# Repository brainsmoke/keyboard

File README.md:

# A numpad-less keyboard with back lighting

TODO: find keycaps which look good with AND without backlight

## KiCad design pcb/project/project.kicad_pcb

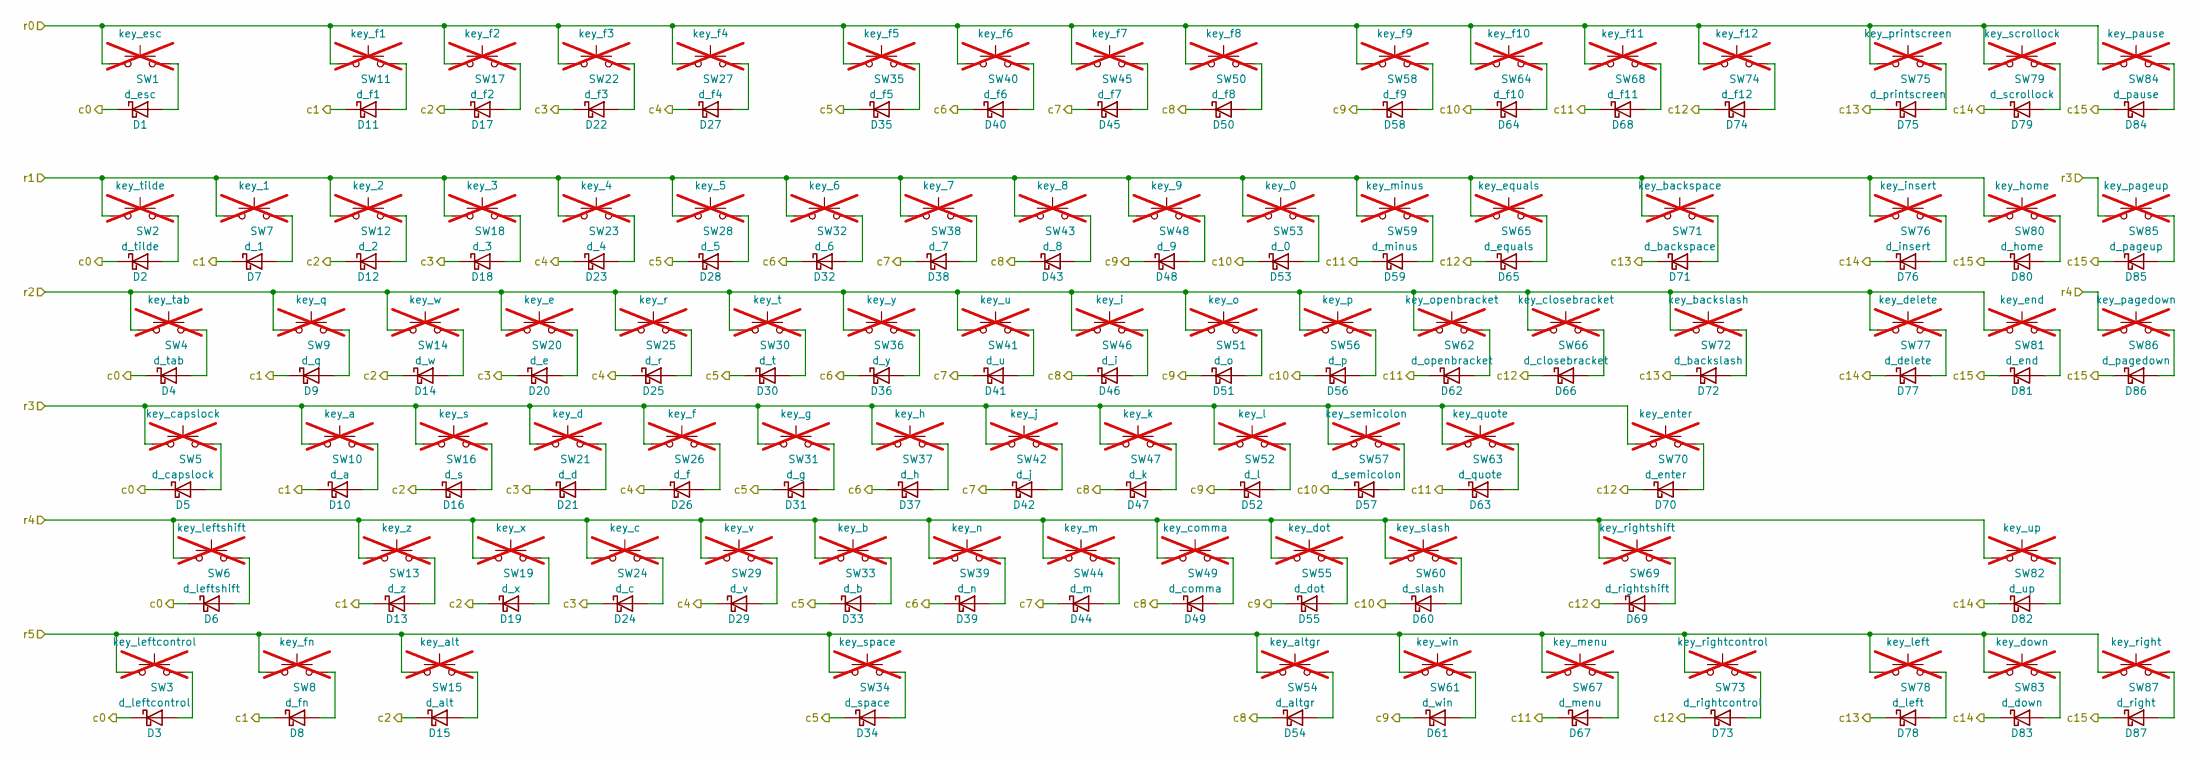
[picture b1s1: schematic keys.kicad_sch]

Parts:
D1: d_esc; D_SOD-123; LCSC C81598
D2: d_tilde; D_SOD-123; LCSC C81598
D3: d_leftcontrol; D_SOD-123; LCSC C81598
D4: d_tab; D_SOD-123; LCSC C81598
D5: d_capslock; D_SOD-123; LCSC C81598
D6: d_leftshift; D_SOD-123; LCSC C81598
D7: d_1; D_SOD-123; LCSC C81598
D8: d_fn; D_SOD-123; LCSC C81598
D9: d_q; D_SOD-123; LCSC C81598
D10: d_a; D_SOD-123; LCSC C81598
D11: d_f1; D_SOD-123; LCSC C81598
D12: d_2; D_SOD-123; LCSC C81598
D13: d_z; D_SOD-123; LCSC C81598
D14: d_w; D_SOD-123; LCSC C81598
D15: d_alt; D_SOD-123; LCSC C81598
D16: d_s; D_SOD-123; LCSC C81598
D17: d_f2; D_SOD-123; LCSC C81598
D18: d_3; D_SOD-123; LCSC C81598
D19: d_x; D_SOD-123; LCSC C81598
D20: d_e; D_SOD-123; LCSC C81598
D21: d_d; D_SOD-123; LCSC C81598
D22: d_f3; D_SOD-123; LCSC C81598
D23: d_4; D_SOD-123; LCSC C81598
D24: d_c; D_SOD-123; LCSC C81598
D25: d_r; D_SOD-123; LCSC C81598
D26: d_f; D_SOD-123; LCSC C81598
D27: d_f4; D_SOD-123; LCSC C81598
D28: d_5; D_SOD-123; LCSC C81598
D29: d_v; D_SOD-123; LCSC C81598
D30: d_t; D_SOD-123; LCSC C81598
D31: d_g; D_SOD-123; LCSC C81598
D32: d_6; D_SOD-123; LCSC C81598
D33: d_b; D_SOD-123; LCSC C81598
D34: d_space; D_SOD-123; LCSC C81598
D35: d_f5; D_SOD-123; LCSC C81598
D36: d_y; D_SOD-123; LCSC C81598
D37: d_h; D_SOD-123; LCSC C81598
D38: d_7; D_SOD-123; LCSC C81598
D39: d_n; D_SOD-123; LCSC C81598
D40: d_f6; D_SOD-123; LCSC C81598
D41: d_u; D_SOD-123; LCSC C81598
D42: d_j; D_SOD-123; LCSC C81598
D43: d_8; D_SOD-123; LCSC C81598
D44: d_m; D_SOD-123; LCSC C81598
D45: d_f7; D_SOD-123; LCSC C81598
D46: d_i; D_SOD-123; LCSC C81598
D47: d_k; D_SOD-123; LCSC C81598
D48: d_9; D_SOD-123; LCSC C81598
D49: d_comma; D_SOD-123; LCSC C81598
D50: d_f8; D_SOD-123; LCSC C81598
D51: d_o; D_SOD-123; LCSC C81598
D52: d_l; D_SOD-123; LCSC C81598
D53: d_0; D_SOD-123; LCSC C81598
D54: d_altgr; D_SOD-123; LCSC C81598
D55: d_dot; D_SOD-123; LCSC C81598
D56: d_p; D_SOD-123; LCSC C81598
D57: d_semicolon; D_SOD-123; LCSC C81598
D58: d_f9; D_SOD-123; LCSC C81598
D59: d_minus; D_SOD-123; LCSC C81598
D60: d_slash; D_SOD-123; LCSC C81598
D61: d_win; D_SOD-123; LCSC C81598
D62: d_openbracket; D_SOD-123; LCSC C81598
D63: d_quote; D_SOD-123; LCSC C81598
D64: d_f10; D_SOD-123; LCSC C81598
D65: d_equals; D_SOD-123; LCSC C81598
D66: d_closebracket; D_SOD-123; LCSC C81598
D67: d_menu; D_SOD-123; LCSC C81598
D68: d_f11; D_SOD-123; LCSC C81598
D69: d_rightshift; D_SOD-123; LCSC C81598
D70: d_enter; D_SOD-123; LCSC C81598
D71: d_backspace; D_SOD-123; LCSC C81598
D72: d_backslash; D_SOD-123; LCSC C81598
D73: d_rightcontrol; D_SOD-123; LCSC C81598
D74: d_f12; D_SOD-123; LCSC C81598
D75: d_printscreen; D_SOD-123; LCSC C81598
D76: d_insert; D_SOD-123; LCSC C81598
D77: d_delete; D_SOD-123; LCSC C81598
D78: d_left; D_SOD-123; LCSC C81598
D79: d_scrollock; D_SOD-123; LCSC C81598
D80: d_home; D_SOD-123; LCSC C81598
D81: d_end; D_SOD-123; LCSC C81598
D82: d_up; D_SOD-123; LCSC C81598
D83: d_down; D_SOD-123; LCSC C81598
D84: d_pause; D_SOD-123; LCSC C81598
D85: d_pageup; D_SOD-123; LCSC C81598
D86: d_pagedown; D_SOD-123; LCSC C81598
D87: d_right; D_SOD-123; LCSC C81598
SW1: key_esc; SW_Cherry_MX_1.00u_PCB; not fitted
SW2: key_tilde; SW_Cherry_MX_1.00u_PCB; not fitted
SW3: key_leftcontrol; SW_Cherry_MX_1.25u_PCB; not fitted
SW4: key_tab; SW_Cherry_MX_1.50u_PCB; not fitted
SW5: key_capslock; SW_Cherry_MX_1.75u_PCB; not fitted
SW6: key_leftshift; SW_Cherry_MX_2.25u_PCB; not fitted
SW7: key_1; SW_Cherry_MX_1.00u_PCB; not fitted
SW8: key_fn; SW_Cherry_MX_1.25u_PCB; not fitted
SW9: key_q; SW_Cherry_MX_1.00u_PCB; not fitted
SW10: key_a; SW_Cherry_MX_1.00u_PCB; not fitted
SW11: key_f1; SW_Cherry_MX_1.00u_PCB; not fitted
SW12: key_2; SW_Cherry_MX_1.00u_PCB; not fitted
SW13: key_z; SW_Cherry_MX_1.00u_PCB; not fitted
SW14: key_w; SW_Cherry_MX_1.00u_PCB; not fitted
SW15: key_alt; SW_Cherry_MX_1.25u_PCB; not fitted
SW16: key_s; SW_Cherry_MX_1.00u_PCB; not fitted
SW17: key_f2; SW_Cherry_MX_1.00u_PCB; not fitted
SW18: key_3; SW_Cherry_MX_1.00u_PCB; not fitted
SW19: key_x; SW_Cherry_MX_1.00u_PCB; not fitted
SW20: key_e; SW_Cherry_MX_1.00u_PCB; not fitted
SW21: key_d; SW_Cherry_MX_1.00u_PCB; not fitted
SW22: key_f3; SW_Cherry_MX_1.00u_PCB; not fitted
SW23: key_4; SW_Cherry_MX_1.00u_PCB; not fitted
SW24: key_c; SW_Cherry_MX_1.00u_PCB; not fitted
SW25: key_r; SW_Cherry_MX_1.00u_PCB; not fitted
SW26: key_f; SW_Cherry_MX_1.00u_PCB; not fitted
SW27: key_f4; SW_Cherry_MX_1.00u_PCB; not fitted
SW28: key_5; SW_Cherry_MX_1.00u_PCB; not fitted
SW29: key_v; SW_Cherry_MX_1.00u_PCB; not fitted
SW30: key_t; SW_Cherry_MX_1.00u_PCB; not fitted
SW31: key_g; SW_Cherry_MX_1.00u_PCB; not fitted
SW32: key_6; SW_Cherry_MX_1.00u_PCB; not fitted
SW33: key_b; SW_Cherry_MX_1.00u_PCB; not fitted
SW34: key_space; SW_Cherry_MX_6.25u_PCB; not fitted
SW35: key_f5; SW_Cherry_MX_1.00u_PCB; not fitted
SW36: key_y; SW_Cherry_MX_1.00u_PCB; not fitted
SW37: key_h; SW_Cherry_MX_1.00u_PCB; not fitted
SW38: key_7; SW_Cherry_MX_1.00u_PCB; not fitted
SW39: key_n; SW_Cherry_MX_1.00u_PCB; not fitted
SW40: key_f6; SW_Cherry_MX_1.00u_PCB; not fitted
SW41: key_u; SW_Cherry_MX_1.00u_PCB; not fitted
SW42: key_j; SW_Cherry_MX_1.00u_PCB; not fitted
SW43: key_8; SW_Cherry_MX_1.00u_PCB; not fitted
SW44: key_m; SW_Cherry_MX_1.00u_PCB; not fitted
SW45: key_f7; SW_Cherry_MX_1.00u_PCB; not fitted
SW46: key_i; SW_Cherry_MX_1.00u_PCB; not fitted
SW47: key_k; SW_Cherry_MX_1.00u_PCB; not fitted
SW48: key_9; SW_Cherry_MX_1.00u_PCB; not fitted
SW49: key_comma; SW_Cherry_MX_1.00u_PCB; not fitted
SW50: key_f8; SW_Cherry_MX_1.00u_PCB; not fitted
SW51: key_o; SW_Cherry_MX_1.00u_PCB; not fitted
SW52: key_l; SW_Cherry_MX_1.00u_PCB; not fitted
SW53: key_0; SW_Cherry_MX_1.00u_PCB; not fitted
SW54: key_altgr; SW_Cherry_MX_1.25u_PCB; not fitted
SW55: key_dot; SW_Cherry_MX_1.00u_PCB; not fitted
SW56: key_p; SW_Cherry_MX_1.00u_PCB; not fitted
SW57: key_semicolon; SW_Cherry_MX_1.00u_PCB; not fitted
SW58: key_f9; SW_Cherry_MX_1.00u_PCB; not fitted
SW59: key_minus; SW_Cherry_MX_1.00u_PCB; not fitted
SW60: key_slash; SW_Cherry_MX_1.00u_PCB; not fitted
SW61: key_win; SW_Cherry_MX_1.25u_PCB; not fitted
SW62: key_openbracket; SW_Cherry_MX_1.00u_PCB; not fitted
SW63: key_quote; SW_Cherry_MX_1.00u_PCB; not fitted
SW64: key_f10; SW_Cherry_MX_1.00u_PCB; not fitted
SW65: key_equals; SW_Cherry_MX_1.00u_PCB; not fitted
SW66: key_closebracket; SW_Cherry_MX_1.00u_PCB; not fitted
SW67: key_menu; SW_Cherry_MX_1.25u_PCB; not fitted
SW68: key_f11; SW_Cherry_MX_1.00u_PCB; not fitted
SW69: key_rightshift; SW_Cherry_MX_2.75u_PCB; not fitted
SW70: key_enter; SW_Cherry_MX_2.25u_PCB; not fitted
SW71: key_backspace; SW_Cherry_MX_2.00u_PCB; not fitted
SW72: key_backslash; SW_Cherry_MX_1.50u_PCB; not fitted
SW73: key_rightcontrol; SW_Cherry_MX_1.25u_PCB; not fitted
SW74: key_f12; SW_Cherry_MX_1.00u_PCB; not fitted
SW75: key_printscreen; SW_Cherry_MX_1.00u_PCB; not fitted
SW76: key_insert; SW_Cherry_MX_1.00u_PCB; not fitted
SW77: key_delete; SW_Cherry_MX_1.00u_PCB; not fitted
SW78: key_left; SW_Cherry_MX_1.00u_PCB; not fitted
SW79: key_scrollock; SW_Cherry_MX_1.00u_PCB; not fitted
SW80: key_home; SW_Cherry_MX_1.00u_PCB; not fitted
SW81: key_end; SW_Cherry_MX_1.00u_PCB; not fitted
SW82: key_up; SW_Cherry_MX_1.00u_PCB; not fitted
SW83: key_down; SW_Cherry_MX_1.00u_PCB; not fitted
SW84: key_pause; SW_Cherry_MX_1.00u_PCB; not fitted
SW85: key_pageup; SW_Cherry_MX_1.00u_PCB; not fitted
SW86: key_pagedown; SW_Cherry_MX_1.00u_PCB; not fitted
SW87: key_right; SW_Cherry_MX_1.00u_PCB; not fitted

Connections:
/C0: D1.1 (K), D2.1 (K), D3.1 (K), D4.1 (K), D5.1 (K), D6.1 (K); also elsewhere on the board
/C1: D7.1 (K), D8.1 (K), D9.1 (K), D10.1 (K), D11.1 (K), D13.1 (K); also elsewhere on the board
/C2: D12.1 (K), D14.1 (K), D15.1 (K), D16.1 (K), D17.1 (K), D19.1 (K); also elsewhere on the board
/C3: D18.1 (K), D20.1 (K), D21.1 (K), D22.1 (K), D24.1 (K); also elsewhere on the board
/C4: D23.1 (K), D25.1 (K), D26.1 (K), D27.1 (K), D29.1 (K); also elsewhere on the board
/C5: D28.1 (K), D30.1 (K), D31.1 (K), D33.1 (K), D34.1 (K), D35.1 (K); also elsewhere on the board
/C6: D32.1 (K), D36.1 (K), D37.1 (K), D39.1 (K), D40.1 (K); also elsewhere on the board
/C7: D38.1 (K), D41.1 (K), D42.1 (K), D44.1 (K), D45.1 (K); also elsewhere on the board
/C8: D43.1 (K), D46.1 (K), D47.1 (K), D49.1 (K), D50.1 (K), D54.1 (K); also elsewhere on the board
/C9: D48.1 (K), D51.1 (K), D52.1 (K), D55.1 (K), D58.1 (K), D61.1 (K); also elsewhere on the board
/C10: D53.1 (K), D56.1 (K), D57.1 (K), D60.1 (K), D64.1 (K); also elsewhere on the board
/C11: D59.1 (K), D62.1 (K), D63.1 (K), D67.1 (K), D68.1 (K); also elsewhere on the board
/C12: D65.1 (K), D66.1 (K), D69.1 (K), D70.1 (K), D73.1 (K), D74.1 (K); also elsewhere on the board
/C13: D71.1 (K), D72.1 (K), D75.1 (K), D78.1 (K); also elsewhere on the board
/C14: D76.1 (K), D77.1 (K), D79.1 (K), D82.1 (K), D83.1 (K); also elsewhere on the board
/C15: D80.1 (K), D81.1 (K), D84.1 (K), D85.1 (K), D86.1 (K), D87.1 (K); also elsewhere on the board
/R0: SW1.1, SW11.1, SW17.1, SW22.1, SW27.1, SW35.1, SW40.1, SW45.1, SW50.1, SW58.1, SW64.1, SW68.1, SW74.1, SW75.1, SW79.1, SW84.1; also elsewhere on the board
/R1: SW2.1, SW7.1, SW12.1, SW18.1, SW23.1, SW28.1, SW32.1, SW38.1, SW43.1, SW48.1, SW53.1, SW59.1, SW65.1, SW71.1, SW76.1, SW80.1; also elsewhere on the board
/R2: SW4.1, SW9.1, SW14.1, SW20.1, SW25.1, SW30.1, SW36.1, SW41.1, SW46.1, SW51.1, SW56.1, SW62.1, SW66.1, SW72.1, SW77.1, SW81.1; also elsewhere on the board
/R3: SW5.1, SW10.1, SW16.1, SW21.1, SW26.1, SW31.1, SW37.1, SW42.1, SW47.1, SW52.1, SW57.1, SW63.1, SW70.1, SW85.1; also elsewhere on the board
/R4: SW6.1, SW13.1, SW19.1, SW24.1, SW29.1, SW33.1, SW39.1, SW44.1, SW49.1, SW55.1, SW60.1, SW69.1, SW82.1, SW86.1; also elsewhere on the board
/R5: SW3.1, SW8.1, SW15.1, SW34.1, SW54.1, SW61.1, SW67.1, SW73.1, SW78.1, SW83.1, SW87.1; also elsewhere on the board
unnamed: D1.2 (A), SW1.2
unnamed: D2.2 (A), SW2.2
unnamed: D3.2 (A), SW3.2
unnamed: D4.2 (A), SW4.2
unnamed: D5.2 (A), SW5.2
unnamed: D6.2 (A), SW6.2
unnamed: D7.2 (A), SW7.2
unnamed: D8.2 (A), SW8.2
unnamed: D9.2 (A), SW9.2
unnamed: D10.2 (A), SW10.2
unnamed: D11.2 (A), SW11.2
unnamed: D12.2 (A), SW12.2
unnamed: D13.2 (A), SW13.2
unnamed: D14.2 (A), SW14.2
unnamed: D15.2 (A), SW15.2
unnamed: D16.2 (A), SW16.2
unnamed: D17.2 (A), SW17.2
unnamed: D18.2 (A), SW18.2
unnamed: D19.2 (A), SW19.2
unnamed: D20.2 (A), SW20.2
unnamed: D21.2 (A), SW21.2
unnamed: D22.2 (A), SW22.2
unnamed: D23.2 (A), SW23.2
unnamed: D24.2 (A), SW24.2
unnamed: D25.2 (A), SW25.2
unnamed: D26.2 (A), SW26.2
unnamed: D27.2 (A), SW27.2
unnamed: D28.2 (A), SW28.2
unnamed: D29.2 (A), SW29.2
unnamed: D30.2 (A), SW30.2
unnamed: D31.2 (A), SW31.2
unnamed: D32.2 (A), SW32.2
unnamed: D33.2 (A), SW33.2
unnamed: D34.2 (A), SW34.2
unnamed: D35.2 (A), SW35.2
unnamed: D36.2 (A), SW36.2
unnamed: D37.2 (A), SW37.2
unnamed: D38.2 (A), SW38.2
unnamed: D39.2 (A), SW39.2
unnamed: D40.2 (A), SW40.2
unnamed: D41.2 (A), SW41.2
unnamed: D42.2 (A), SW42.2
unnamed: D43.2 (A), SW43.2
unnamed: D44.2 (A), SW44.2
unnamed: D45.2 (A), SW45.2
unnamed: D46.2 (A), SW46.2
unnamed: D47.2 (A), SW47.2
unnamed: D48.2 (A), SW48.2
unnamed: D49.2 (A), SW49.2
unnamed: D50.2 (A), SW50.2
unnamed: D51.2 (A), SW51.2
unnamed: D52.2 (A), SW52.2
unnamed: D53.2 (A), SW53.2
unnamed: D54.2 (A), SW54.2
unnamed: D55.2 (A), SW55.2
unnamed: D56.2 (A), SW56.2
unnamed: D57.2 (A), SW57.2
unnamed: D58.2 (A), SW58.2
unnamed: D59.2 (A), SW59.2
unnamed: D60.2 (A), SW60.2
unnamed: D61.2 (A), SW61.2
unnamed: D62.2 (A), SW62.2
unnamed: D63.2 (A), SW63.2
unnamed: D64.2 (A), SW64.2
unnamed: D65.2 (A), SW65.2
unnamed: D66.2 (A), SW66.2
unnamed: D67.2 (A), SW67.2
unnamed: D68.2 (A), SW68.2
unnamed: D69.2 (A), SW69.2
unnamed: D70.2 (A), SW70.2
unnamed: D71.2 (A), SW71.2
unnamed: D72.2 (A), SW72.2
unnamed: D73.2 (A), SW73.2
unnamed: D74.2 (A), SW74.2
unnamed: D75.2 (A), SW75.2
unnamed: D76.2 (A), SW76.2
unnamed: D77.2 (A), SW77.2
unnamed: D78.2 (A), SW78.2
unnamed: D79.2 (A), SW79.2
unnamed: D80.2 (A), SW80.2
unnamed: D81.2 (A), SW81.2
unnamed: D82.2 (A), SW82.2
unnamed: D83.2 (A), SW83.2
unnamed: D84.2 (A), SW84.2
unnamed: D85.2 (A), SW85.2
unnamed: D86.2 (A), SW86.2
unnamed: D87.2 (A), SW87.2

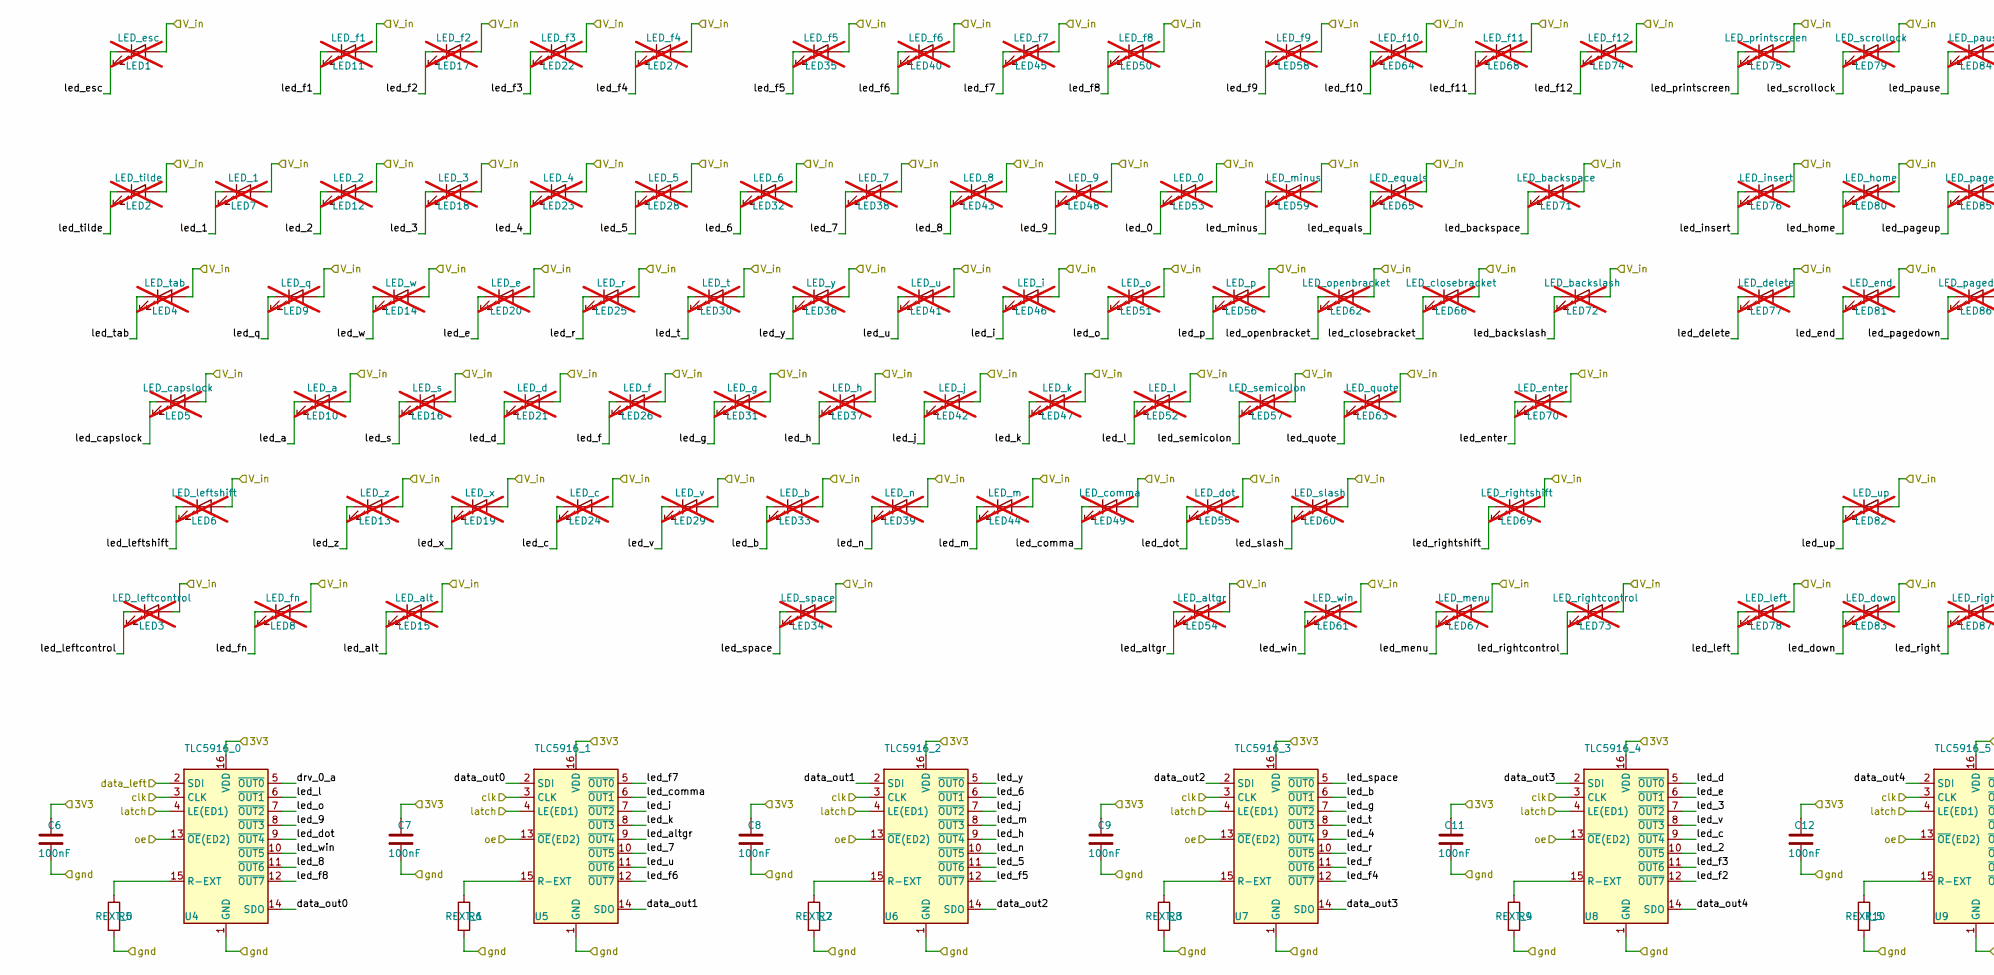
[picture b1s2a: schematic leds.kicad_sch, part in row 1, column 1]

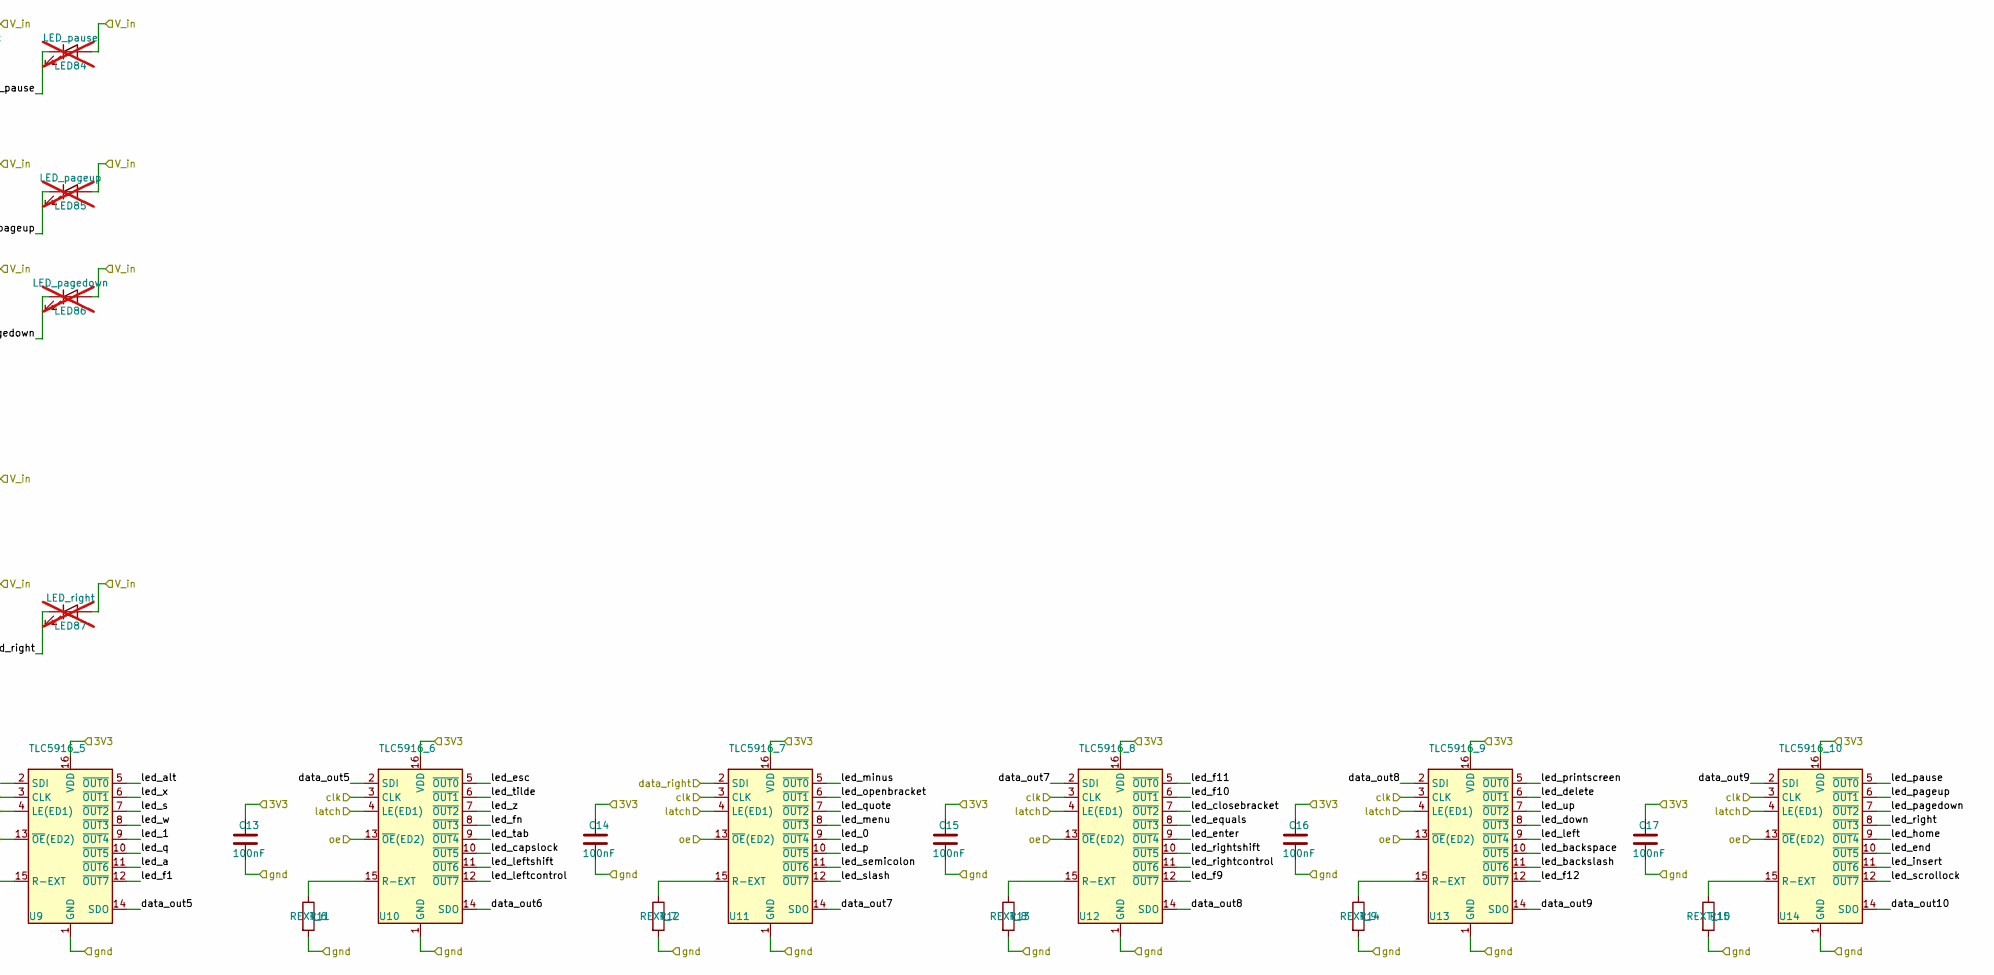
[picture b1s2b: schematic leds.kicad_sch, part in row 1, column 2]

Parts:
C6, C7, C8, C9, C11, C12, C13, C14, C15, C16, C17: 100nF; C_0402_1005Metric; LCSC C1525
LED1: LED_esc; LED3mm; not fitted
LED2: LED_tilde; LED3mm; not fitted
LED3: LED_leftcontrol; LED3mm; not fitted
LED4: LED_tab; LED3mm; not fitted
LED5: LED_capslock; LED3mm; not fitted
LED6: LED_leftshift; LED3mm; not fitted
LED7: LED_1; LED3mm; not fitted
LED8: LED_fn; LED3mm; not fitted
LED9: LED_q; LED3mm; not fitted
LED10: LED_a; LED3mm; not fitted
LED11: LED_f1; LED3mm; not fitted
LED12: LED_2; LED3mm; not fitted
LED13: LED_z; LED3mm; not fitted
LED14: LED_w; LED3mm; not fitted
LED15: LED_alt; LED3mm; not fitted
LED16: LED_s; LED3mm; not fitted
LED17: LED_f2; LED3mm; not fitted
LED18: LED_3; LED3mm; not fitted
LED19: LED_x; LED3mm; not fitted
LED20: LED_e; LED3mm; not fitted
LED21: LED_d; LED3mm; not fitted
LED22: LED_f3; LED3mm; not fitted
LED23: LED_4; LED3mm; not fitted
LED24: LED_c; LED3mm; not fitted
LED25: LED_r; LED3mm; not fitted
LED26: LED_f; LED3mm; not fitted
LED27: LED_f4; LED3mm; not fitted
LED28: LED_5; LED3mm; not fitted
LED29: LED_v; LED3mm; not fitted
LED30: LED_t; LED3mm; not fitted
LED31: LED_g; LED3mm; not fitted
LED32: LED_6; LED3mm; not fitted
LED33: LED_b; LED3mm; not fitted
LED34: LED_space; LED3mm; not fitted
LED35: LED_f5; LED3mm; not fitted
LED36: LED_y; LED3mm; not fitted
LED37: LED_h; LED3mm; not fitted
LED38: LED_7; LED3mm; not fitted
LED39: LED_n; LED3mm; not fitted
LED40: LED_f6; LED3mm; not fitted
LED41: LED_u; LED3mm; not fitted
LED42: LED_j; LED3mm; not fitted
LED43: LED_8; LED3mm; not fitted
LED44: LED_m; LED3mm; not fitted
LED45: LED_f7; LED3mm; not fitted
LED46: LED_i; LED3mm; not fitted
LED47: LED_k; LED3mm; not fitted
LED48: LED_9; LED3mm; not fitted
LED49: LED_comma; LED3mm; not fitted
LED50: LED_f8; LED3mm; not fitted
LED51: LED_o; LED3mm; not fitted
LED52: LED_l; LED3mm; not fitted
LED53: LED_0; LED3mm; not fitted
LED54: LED_altgr; LED3mm; not fitted
LED55: LED_dot; LED3mm; not fitted
LED56: LED_p; LED3mm; not fitted
LED57: LED_semicolon; LED3mm; not fitted
LED58: LED_f9; LED3mm; not fitted
LED59: LED_minus; LED3mm; not fitted
LED60: LED_slash; LED3mm; not fitted
LED61: LED_win; LED3mm; not fitted
LED62: LED_openbracket; LED3mm; not fitted
LED63: LED_quote; LED3mm; not fitted
LED64: LED_f10; LED3mm; not fitted
LED65: LED_equals; LED3mm; not fitted
LED66: LED_closebracket; LED3mm; not fitted
LED67: LED_menu; LED3mm; not fitted
LED68: LED_f11; LED3mm; not fitted
LED69: LED_rightshift; LED3mm; not fitted
LED70: LED_enter; LED3mm; not fitted
LED71: LED_backspace; LED3mm; not fitted
LED72: LED_backslash; LED3mm; not fitted
LED73: LED_rightcontrol; LED3mm; not fitted
LED74: LED_f12; LED3mm; not fitted
LED75: LED_printscreen; LED3mm; not fitted
LED76: LED_insert; LED3mm; not fitted
LED77: LED_delete; LED3mm; not fitted
LED78: LED_left; LED3mm; not fitted
LED79: LED_scrollock; LED3mm; not fitted
LED80: LED_home; LED3mm; not fitted
LED81: LED_end; LED3mm; not fitted
LED82: LED_up; LED3mm; not fitted
LED83: LED_down; LED3mm; not fitted
LED84: LED_pause; LED3mm; not fitted
LED85: LED_pageup; LED3mm; not fitted
LED86: LED_pagedown; LED3mm; not fitted
LED87: LED_right; LED3mm; not fitted
R5: REXT_0; R_0402_1005Metric; LCSC C25905
R6: REXT_1; R_0402_1005Metric; LCSC C25905
R7: REXT_2; R_0402_1005Metric; LCSC C25905
R8: REXT_3; R_0402_1005Metric; LCSC C25905
R9: REXT_4; R_0402_1005Metric; LCSC C25905
R10: REXT_5; R_0402_1005Metric; LCSC C25905
R11: REXT_6; R_0402_1005Metric; LCSC C25905
R12: REXT_7; R_0402_1005Metric; LCSC C25905
R13: REXT_8; R_0402_1005Metric; LCSC C25905
R14: REXT_9; R_0402_1005Metric; LCSC C25905
R15: REXT_10; R_0402_1005Metric; LCSC C25905
U4: TLC5916_0; TSSOP-16_4.4x5mm_P0.65mm; LCSC C2678539
U5: TLC5916_1; TSSOP-16_4.4x5mm_P0.65mm; LCSC C2678539
U6: TLC5916_2; TSSOP-16_4.4x5mm_P0.65mm; LCSC C2678539
U7: TLC5916_3; TSSOP-16_4.4x5mm_P0.65mm; LCSC C2678539
U8: TLC5916_4; TSSOP-16_4.4x5mm_P0.65mm; LCSC C2678539
U9: TLC5916_5; TSSOP-16_4.4x5mm_P0.65mm; LCSC C2678539
U10: TLC5916_6; TSSOP-16_4.4x5mm_P0.65mm; LCSC C2678539
U11: TLC5916_7; TSSOP-16_4.4x5mm_P0.65mm; LCSC C2678539
U12: TLC5916_8; TSSOP-16_4.4x5mm_P0.65mm; LCSC C2678539
U13: TLC5916_9; TSSOP-16_4.4x5mm_P0.65mm; LCSC C2678539
U14: TLC5916_10; TSSOP-16_4.4x5mm_P0.65mm; LCSC C2678539

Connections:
3V3: C6.1, C7.1, C8.1, C9.1, C11.1, C12.1, C13.1, C14.1, C15.1, C16.1, C17.1, U4.16 (VDD), U5.16 (VDD), U6.16 (VDD), U7.16 (VDD), U8.16 (VDD), U9.16 (VDD), U10.16 (VDD), U11.16 (VDD), U12.16 (VDD), U13.16 (VDD), U14.16 (VDD); also elsewhere on the board
5V: LED1.2 (A), LED2.2 (A), LED3.2 (A), LED4.2 (A), LED5.2 (A), LED6.2 (A), LED7.2 (A), LED8.2 (A), LED9.2 (A), LED10.2 (A), LED11.2 (A), LED12.2 (A), LED13.2 (A), LED14.2 (A), LED15.2 (A), LED16.2 (A), LED17.2 (A), LED18.2 (A), LED19.2 (A), LED20.2 (A), LED21.2 (A), LED22.2 (A), LED23.2 (A), LED24.2 (A), LED25.2 (A), LED26.2 (A), LED27.2 (A), LED28.2 (A), LED29.2 (A), LED30.2 (A), LED31.2 (A), LED32.2 (A), LED33.2 (A), LED34.2 (A), LED35.2 (A), LED36.2 (A), LED37.2 (A), LED38.2 (A), LED39.2 (A), LED40.2 (A), LED41.2 (A), LED42.2 (A), LED43.2 (A), LED44.2 (A), LED45.2 (A), LED46.2 (A), LED47.2 (A), LED48.2 (A), LED49.2 (A), LED50.2 (A), LED51.2 (A), LED52.2 (A), LED53.2 (A), LED54.2 (A), LED55.2 (A), LED56.2 (A), LED57.2 (A), LED58.2 (A), LED59.2 (A), LED60.2 (A), LED61.2 (A), LED62.2 (A), LED63.2 (A), LED64.2 (A), LED65.2 (A), LED66.2 (A), LED67.2 (A), LED68.2 (A), LED69.2 (A), LED70.2 (A), LED71.2 (A), LED72.2 (A), LED73.2 (A), LED74.2 (A), LED75.2 (A), LED76.2 (A), LED77.2 (A), LED78.2 (A), LED79.2 (A), LED80.2 (A), LED81.2 (A), LED82.2 (A), LED83.2 (A), LED84.2 (A), LED85.2 (A), LED86.2 (A), LED87.2 (A); also elsewhere on the board
/LEDs/clk: U4.3 (CLK), U5.3 (CLK), U6.3 (CLK), U7.3 (CLK), U8.3 (CLK), U9.3 (CLK), U10.3 (CLK), U11.3 (CLK), U12.3 (CLK), U13.3 (CLK), U14.3 (CLK); also elsewhere on the board
/LEDs/data_left: U4.2 (SDI); also elsewhere on the board
/LEDs/data_out0: U4.14 (SDO), U5.2 (SDI)
/LEDs/data_out1: U5.14 (SDO), U6.2 (SDI)
/LEDs/data_out2: U6.14 (SDO), U7.2 (SDI)
/LEDs/data_out3: U7.14 (SDO), U8.2 (SDI)
/LEDs/data_out4: U8.14 (SDO), U9.2 (SDI)
/LEDs/data_out5: U9.14 (SDO), U10.2 (SDI)
/LEDs/data_out6: U10.14 (SDO)
/LEDs/data_out7: U11.14 (SDO), U12.2 (SDI)
/LEDs/data_out8: U12.14 (SDO), U13.2 (SDI)
/LEDs/data_out9: U13.14 (SDO), U14.2 (SDI)
/LEDs/data_out10: U14.14 (SDO)
/LEDs/data_right: U11.2 (SDI); also elsewhere on the board
/LEDs/drv_0_a: U4.5 (~OUT0)
/LEDs/latch: U4.4 (LE(ED1)), U5.4 (LE(ED1)), U6.4 (LE(ED1)), U7.4 (LE(ED1)), U8.4 (LE(ED1)), U9.4 (LE(ED1)), U10.4 (LE(ED1)), U11.4 (LE(ED1)), U12.4 (LE(ED1)), U13.4 (LE(ED1)), U14.4 (LE(ED1)); also elsewhere on the board
/LEDs/led_0: LED53.1 (K), U11.9 (~OUT4)
/LEDs/led_1: LED7.1 (K), U9.9 (~OUT4)
/LEDs/led_2: LED12.1 (K), U8.10 (~OUT5)
/LEDs/led_3: LED18.1 (K), U8.7 (~OUT2)
/LEDs/led_4: LED23.1 (K), U7.9 (~OUT4)
/LEDs/led_5: LED28.1 (K), U6.11 (~OUT6)
/LEDs/led_6: LED32.1 (K), U6.6 (~OUT1)
/LEDs/led_7: LED38.1 (K), U5.10 (~OUT5)
/LEDs/led_8: LED43.1 (K), U4.11 (~OUT6)
/LEDs/led_9: LED48.1 (K), U4.8 (~OUT3)
/LEDs/led_a: LED10.1 (K), U9.11 (~OUT6)
/LEDs/led_alt: LED15.1 (K), U9.5 (~OUT0)
/LEDs/led_altgr: LED54.1 (K), U5.9 (~OUT4)
/LEDs/led_b: LED33.1 (K), U7.6 (~OUT1)
/LEDs/led_backslash: LED72.1 (K), U13.11 (~OUT6)
/LEDs/led_backspace: LED71.1 (K), U13.10 (~OUT5)
/LEDs/led_c: LED24.1 (K), U8.9 (~OUT4)
/LEDs/led_capslock: LED5.1 (K), U10.10 (~OUT5)
/LEDs/led_closebracket: LED66.1 (K), U12.7 (~OUT2)
/LEDs/led_comma: LED49.1 (K), U5.6 (~OUT1)
/LEDs/led_d: LED21.1 (K), U8.5 (~OUT0)
/LEDs/led_delete: LED77.1 (K), U13.6 (~OUT1)
/LEDs/led_dot: LED55.1 (K), U4.9 (~OUT4)
/LEDs/led_down: LED83.1 (K), U13.8 (~OUT3)
/LEDs/led_e: LED20.1 (K), U8.6 (~OUT1)
/LEDs/led_end: LED81.1 (K), U14.10 (~OUT5)
/LEDs/led_enter: LED70.1 (K), U12.9 (~OUT4)
/LEDs/led_equals: LED65.1 (K), U12.8 (~OUT3)
/LEDs/led_esc: LED1.1 (K), U10.5 (~OUT0)
/LEDs/led_f: LED26.1 (K), U7.11 (~OUT6)
/LEDs/led_f1: LED11.1 (K), U9.12 (~OUT7)
/LEDs/led_f2: LED17.1 (K), U8.12 (~OUT7)
/LEDs/led_f3: LED22.1 (K), U8.11 (~OUT6)
/LEDs/led_f4: LED27.1 (K), U7.12 (~OUT7)
/LEDs/led_f5: LED35.1 (K), U6.12 (~OUT7)
/LEDs/led_f6: LED40.1 (K), U5.12 (~OUT7)
/LEDs/led_f7: LED45.1 (K), U5.5 (~OUT0)
/LEDs/led_f8: LED50.1 (K), U4.12 (~OUT7)
/LEDs/led_f9: LED58.1 (K), U12.12 (~OUT7)
/LEDs/led_f10: LED64.1 (K), U12.6 (~OUT1)
/LEDs/led_f11: LED68.1 (K), U12.5 (~OUT0)
/LEDs/led_f12: LED74.1 (K), U13.12 (~OUT7)
/LEDs/led_fn: LED8.1 (K), U10.8 (~OUT3)
/LEDs/led_g: LED31.1 (K), U7.7 (~OUT2)
/LEDs/led_h: LED37.1 (K), U6.9 (~OUT4)
/LEDs/led_home: LED80.1 (K), U14.9 (~OUT4)
/LEDs/led_i: LED46.1 (K), U5.7 (~OUT2)
/LEDs/led_insert: LED76.1 (K), U14.11 (~OUT6)
/LEDs/led_j: LED42.1 (K), U6.7 (~OUT2)
/LEDs/led_k: LED47.1 (K), U5.8 (~OUT3)
/LEDs/led_l: LED52.1 (K), U4.6 (~OUT1)
/LEDs/led_left: LED78.1 (K), U13.9 (~OUT4)
/LEDs/led_leftcontrol: LED3.1 (K), U10.12 (~OUT7)
/LEDs/led_leftshift: LED6.1 (K), U10.11 (~OUT6)
/LEDs/led_m: LED44.1 (K), U6.8 (~OUT3)
/LEDs/led_menu: LED67.1 (K), U11.8 (~OUT3)
/LEDs/led_minus: LED59.1 (K), U11.5 (~OUT0)
/LEDs/led_n: LED39.1 (K), U6.10 (~OUT5)
/LEDs/led_o: LED51.1 (K), U4.7 (~OUT2)
/LEDs/led_openbracket: LED62.1 (K), U11.6 (~OUT1)
/LEDs/led_p: LED56.1 (K), U11.10 (~OUT5)
/LEDs/led_pagedown: LED86.1 (K), U14.7 (~OUT2)
/LEDs/led_pageup: LED85.1 (K), U14.6 (~OUT1)
/LEDs/led_pause: LED84.1 (K), U14.5 (~OUT0)
/LEDs/led_printscreen: LED75.1 (K), U13.5 (~OUT0)
/LEDs/led_q: LED9.1 (K), U9.10 (~OUT5)
/LEDs/led_quote: LED63.1 (K), U11.7 (~OUT2)
/LEDs/led_r: LED25.1 (K), U7.10 (~OUT5)
/LEDs/led_right: LED87.1 (K), U14.8 (~OUT3)
/LEDs/led_rightcontrol: LED73.1 (K), U12.11 (~OUT6)
/LEDs/led_rightshift: LED69.1 (K), U12.10 (~OUT5)
/LEDs/led_s: LED16.1 (K), U9.7 (~OUT2)
/LEDs/led_scrollock: LED79.1 (K), U14.12 (~OUT7)
/LEDs/led_semicolon: LED57.1 (K), U11.11 (~OUT6)
/LEDs/led_slash: LED60.1 (K), U11.12 (~OUT7)
/LEDs/led_space: LED34.1 (K), U7.5 (~OUT0)
/LEDs/led_t: LED30.1 (K), U7.8 (~OUT3)
/LEDs/led_tab: LED4.1 (K), U10.9 (~OUT4)
/LEDs/led_tilde: LED2.1 (K), U10.6 (~OUT1)
/LEDs/led_u: LED41.1 (K), U5.11 (~OUT6)
/LEDs/led_up: LED82.1 (K), U13.7 (~OUT2)
/LEDs/led_v: LED29.1 (K), U8.8 (~OUT3)
/LEDs/led_w: LED14.1 (K), U9.8 (~OUT3)
/LEDs/led_win: LED61.1 (K), U4.10 (~OUT5)
/LEDs/led_x: LED19.1 (K), U9.6 (~OUT1)
/LEDs/led_y: LED36.1 (K), U6.5 (~OUT0)
/LEDs/led_z: LED13.1 (K), U10.7 (~OUT2)
/LEDs/oe: U4.13 (~OE(ED2)), U5.13 (~OE(ED2)), U6.13 (~OE(ED2)), U7.13 (~OE(ED2)), U8.13 (~OE(ED2)), U9.13 (~OE(ED2)), U10.13 (~OE(ED2)), U11.13 (~OE(ED2)), U12.13 (~OE(ED2)), U13.13 (~OE(ED2)), U14.13 (~OE(ED2)); also elsewhere on the board
GND: C6.2, C7.2, C8.2, C9.2, C11.2, C12.2, C13.2, C14.2, C15.2, C16.2, C17.2, R5.2, R6.2, R7.2, R8.2, R9.2, R10.2, R11.2, R12.2, R13.2, R14.2, R15.2, U4.1 (GND), U5.1 (GND), U6.1 (GND), U7.1 (GND), U8.1 (GND), U9.1 (GND), U10.1 (GND), U11.1 (GND), U12.1 (GND), U13.1 (GND), U14.1 (GND); also elsewhere on the board
unnamed: R5.1, U4.15 (R-EXT)
unnamed: R6.1, U5.15 (R-EXT)
unnamed: R7.1, U6.15 (R-EXT)
unnamed: R8.1, U7.15 (R-EXT)
unnamed: R9.1, U8.15 (R-EXT)
unnamed: R10.1, U9.15 (R-EXT)
unnamed: R11.1, U10.15 (R-EXT)
unnamed: R12.1, U11.15 (R-EXT)
unnamed: R13.1, U12.15 (R-EXT)
unnamed: R14.1, U13.15 (R-EXT)
unnamed: R15.1, U14.15 (R-EXT)

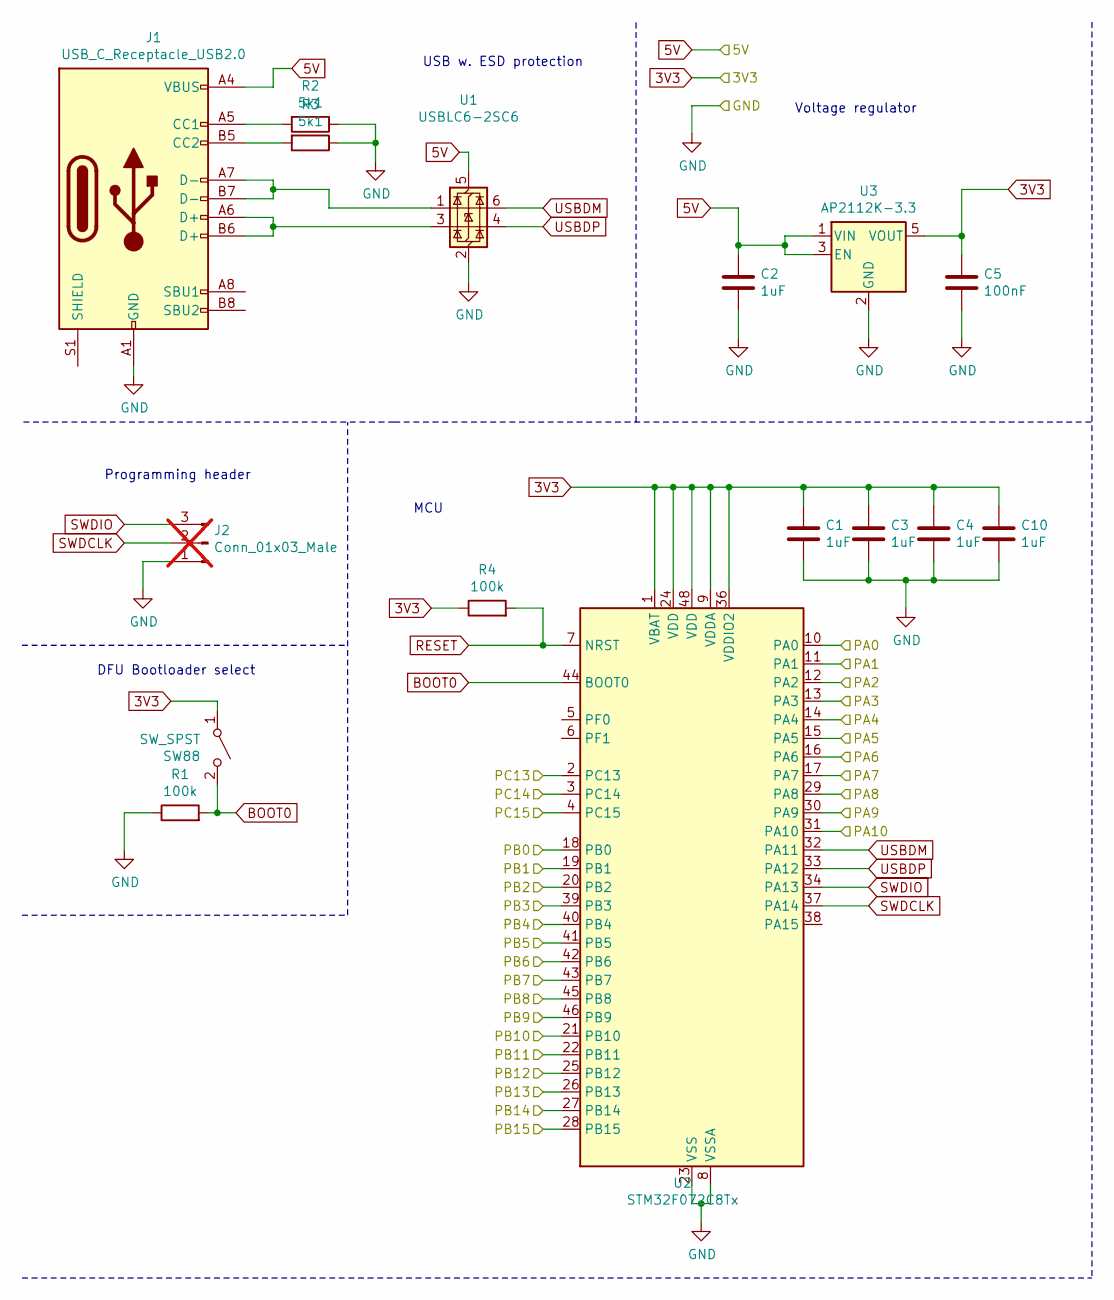
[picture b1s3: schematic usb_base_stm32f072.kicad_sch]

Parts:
C1, C2, C3, C4, C10: 1uF; C_0402_1005Metric; LCSC C52923
C5: 100nF; C_0402_1005Metric; LCSC C1525
J1: USB_C_Receptacle_USB2.0; USB_C_Receptacle_HRO_TYPE-C-31-M-12; LCSC C165948
J2: Conn_01x03_Male; PinHeader_1x03_P2.54mm_Vertical; not fitted
R1, R4: 100k; R_0402_1005Metric; LCSC C25741
R2, R3: 5k1; R_0402_1005Metric; LCSC C25905
SW88: SW_SPST; SW_Push_1P1T_NO_CK_KMR2; LCSC C318893
U1: USBLC6-2SC6; SOT-23-6; LCSC C7519
U2: STM32F072C8Tx; LQFP-48_7x7mm_P0.5mm; LCSC C81720
U3: AP2112K-3.3; SOT-23-5; LCSC C51118

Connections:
3V3: C1.1, C3.1, C4.1, C5.1, C10.1, R4.1, SW88.1 (A), U2.1 (VBAT), U2.9 (VDDA), U2.24 (VDD), U2.36 (VDDIO2), U2.48 (VDD), U3.5 (VOUT); also elsewhere on the board
5V: C2.1, J1.A4 (VBUS), J1.A9 (VBUS), J1.B4 (VBUS), J1.B9 (VBUS), U1.5 (VBUS), U3.1 (VIN), U3.3 (EN); also elsewhere on the board
/C0: U2.28 (PB15); also elsewhere on the board
/C1: U2.27 (PB14); also elsewhere on the board
/C2: U2.26 (PB13); also elsewhere on the board
/C3: U2.25 (PB12); also elsewhere on the board
/C4: U2.22 (PB11); also elsewhere on the board
/C5: U2.21 (PB10); also elsewhere on the board
/C6: U2.20 (PB2); also elsewhere on the board
/C7: U2.19 (PB1); also elsewhere on the board
/C8: U2.18 (PB0); also elsewhere on the board
/C9: U2.42 (PB6); also elsewhere on the board
/C10: U2.46 (PB9); also elsewhere on the board
/C11: U2.45 (PB8); also elsewhere on the board
/C12: U2.43 (PB7); also elsewhere on the board
/C13: U2.41 (PB5); also elsewhere on the board
/C14: U2.40 (PB4); also elsewhere on the board
/C15: U2.39 (PB3); also elsewhere on the board
/LEDs/clk: U2.3 (PC14); also elsewhere on the board
/LEDs/data_left: U2.4 (PC15); also elsewhere on the board
/LEDs/data_right: U2.2 (PC13); also elsewhere on the board
/LEDs/latch: U2.10 (PA0); also elsewhere on the board
/LEDs/oe: U2.11 (PA1); also elsewhere on the board
/R0: U2.17 (PA7); also elsewhere on the board
/R1: U2.12 (PA2); also elsewhere on the board
/R2: U2.13 (PA3); also elsewhere on the board
/R3: U2.14 (PA4); also elsewhere on the board
/R4: U2.15 (PA5); also elsewhere on the board
/R5: U2.16 (PA6); also elsewhere on the board
/usb_base/PA8: U2.29 (PA8)
/usb_base/PA9: U2.30 (PA9)
/usb_base/PA10: U2.31 (PA10)
BOOT0: R1.2, SW88.2 (B), U2.44 (BOOT0)
GND: C1.2, C2.2, C3.2, C4.2, C5.2, C10.2, J1.A1 (GND), J1.A12 (GND), J1.B1 (GND), J1.B12 (GND), J2.1, R1.1, R2.1, R3.1, U1.2 (GND), U2.8 (VSSA), U2.23 (VSS), U2.35 (VSS), U2.47 (VSS), U3.2 (GND); also elsewhere on the board
unnamed: J1.A5 (CC1), R2.2
unnamed: J1.B5 (CC2), R3.2
unnamed: J1.A6 (D+), J1.B6 (D+), U1.3 (I/O2)
unnamed: J1.A7 (D-), J1.B7 (D-), U1.1 (I/O1)
RESET: R4.2, U2.7 (NRST)
SWDCLK: J2.2, U2.37 (PA14)
SWDIO: J2.3, U2.34 (PA13)
USBDM: U1.6 (I/O1), U2.32 (PA11)
USBDP: U1.4 (I/O2), U2.33 (PA12)

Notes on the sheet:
Programming header
DFU Bootloader select
Voltage regulator
MCU
USB w. ESD protection

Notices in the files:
pcb/project/project.kicad_pcb:
CC-BY-4.0
